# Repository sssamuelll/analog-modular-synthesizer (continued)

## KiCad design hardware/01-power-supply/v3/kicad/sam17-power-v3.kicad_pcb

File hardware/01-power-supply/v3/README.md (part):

# PSU v3 — la primera que se construye

> **ESTADO, 2026-09-04: la v3 NO se pide.** La que se construye es la **v4**
> ([`../v4/`](../v4/)): seis módulos Mean Well IRM encapsulados en vez del
> toroide, con la misma cascada lineal detrás. La gobierna
> [`2026-09-03-fuente-v4-liston-design.md`](../../../docs/superpowers/specs/2026-09-03-fuente-v4-liston-design.md).
>
> Lo que esta carpeta conserva y sigue valiendo: **la cascada** (`U1`/`U2` y la
> isla LT3045/LT3094) con sus puertas, el bus board, la telemetría y el
> bring-up de la cascada. La v4 la hereda entera menos `TR1`, `BR1`, `C_bulk`
> y la franja de red, que se van a la placa R nueva.
>
> **La regla de esta carpeta —«lo que no quede decidido sale con huella y
> `DNP`, nunca con una v4»— NO se reexpide, y el papel de la v4 dice por qué**
> (§0): sus huecos «no son huellas —son chapa, fusible, una placa entera— y
> una regla que no puede aplicarse a sí misma no gobierna». Lo que se impone
> en su lugar es más duro y verificable: **nada de la v4 se manda a fabricar
> con un ítem de §12 abierto**, y eso lo hacen cumplir las puertas de §9, no
> una frase.
>
> Dónde está eso hoy, con número: `hardware/tools/gates.py` (45 en verde, 0 en
> rojo) y `../v4/check_bringup.py` (75 puntos, ninguno medido, porque la placa
> R no existe).
>
> `valle_budget.py` se borró el 2026-09-04: medía el valle de VRAW y la v4 no
> tiene rectificador. Lo sustituye
> [`../v4/margen_budget.py`](../v4/margen_budget.py), que hoy declara un HUECO
> —al riel ultra le faltan 97 mV de margen de entrada en su peor caso— y es
> una decisión abierta, no un fallo de guion.

**Estado:** Fases A (decisiones), B (esquemático), C (placa) y D (chasis)
cerradas. La placa está **ruteada y con DRC en cero**; falta la validación —
que empieza cuando exista la placa física.

> **La v1 y la v2 son diseños de papel.** La v1 se abandonó el 2026-08-17 sin
> fabricar; la v2 llegó a tener gerbers, BOM y CPL generados y tampoco se pidió.
> Ésta es la tercera y la primera que existe como objeto. De ahí su constraint:
> **lo que no quede decidido sale con huella y `DNP`, nunca con una v4.**

## Qué cambia respecto de la v2

La topología de regulación **no se toca**: sigue siendo la cascada de dos etapas
por riel, con las mismas piezas y los mismos setpoints. Lo que cambia es todo lo
que la rodea.

| | v2 | v3 | por qué |
|---|---|---|---|
| **Disipación** | 3 disipadores Fischer individuales | los tabs contra la pared del chasis | Tj de `U2`: 101 → **62 °C** |
| **Colocación de los TO-220** | diagonal opuesta a la isla SMD | en fila sobre un canto, **tabs coplanares** | lo impone la pared, no la estética |
| **Protección** | crowbar en +12 V | **ninguno, en ningún riel** | #118 |
| **Fusible de red** | `F1` en la placa | en el **IEC C14 de la pared** | #130 |
| **Instrumentación** | 6 test points | test points + **isla de telemetría** | spec §4 |

### La protección: no se sustituye, se retira

El crowbar de la v2 protegía contra un fallo del regulador que pusiera VRAW en
el bus. Al rehacer el análisis contra el BOM real (§16.8, reescrita) salieron dos
cosas a la vez:

- **La cascada ya protege sola.** Ningún fallo *simple* pone más de ±13,1 V en el
  bus, que está dentro del máximo absoluto de todos los chips del instrumento. Y
  el pre-regulador no arrastra al post: los LT3045/LT3094 aguantan los 20,54 V de
  VRAW con 1,46 V de margen (ADI Rev. D p.2 / Rev. B p.3).
- **El lazo del crowbar no cerraba con ningún SCR.** El fusible tiene que abrir
  para que el corto sirva de algo, y `F1` subió de 250 mA a 1,6 A en la v2 —
  correctamente, por el inrush del toroide. A los 2,79 A que refleja el fallo,
  IEC 60127 **no obliga** a un fusible T a abrir. El SCR muere en 140 µs; el
  fusible tarda entre 1,3 y 3,9 s.

> El fallo del guardaespaldas es peor que el peligro del que cuida.

Lo que **no** se va con el crowbar: **un TR1 sin fusible térmico embebido no se
compra.** Los 642 W de cualquier corto del secundario son la cuenta que ni `F1`
ni un crowbar cubren, y esto pasa dentro de un recinto cerrado.

## Las puertas

Quince, todas ejecutables, todas recogidas por `hardware/tools/gates.py` sin
tener que apuntarlas en ninguna lista — se añade una escribiendo el fichero,
nunca ampliando un índice que alguien puede olvidar:

| Puerta | Qué pregunta |
|---|---|
| [`check_absmax.py`](check_absmax.py) | ¿sobreviven los módulos a un fallo de regulador? Y antes de eso: ¿la cascada **existe**? |
| [`check_telemetria.py`](check_telemetria.py) | ¿el instrumento sobrevive a medir? Divisores, shunts, direcciones I²C y alimentaciones contra el límite garantizado de cada datasheet |
| [`kicad/check_bom.py`](kicad/check_bom.py) | ¿el BOM y la hoja tienen los mismos designadores? |
| [`kicad/check_netlist.py`](kicad/check_netlist.py) | ¿la isla está **cableada** como dice el contrato? Shunts en serie, divisores en el sentido correcto, masas sin un nodo común |
| [`kicad/check_pcb.py`](kicad/check_pcb.py) | ¿la placa **commiteada** está colocada como dice el script, y su cobre guardado cumple cruces, **masa en árbol sin ni un bucle —vías incluidas—**, cero conexiones abiertas, cero muñones colgando, pista–pad y separación de vías? También vigila la barrera de red, la isla de referencia, la diagonal del lazo y los tres tabs contra la pared |
| [`kicad/check_pcb_mutations.py`](kicad/check_pcb_mutations.py) | ¿las siete mutaciones históricas —pieza movida, cruce, bucle de masa en una capa, bucle que cruza de capa por una vía, muñón colgando, pista sobre pad y vía duplicada— siguen poniendo roja la puerta completa, **cada una por separado y con el número de líneas que su fila declara**? Más los umbrales del filtro de cajas, los rechazos de cobre que no sabe leer, y que una vía de masa quitada deja una conexión abierta |
| [`check_paquete.py`](check_paquete.py) | ¿el paquete de fabricación commiteado es **el de esta placa**? Cruza los trazos de los dos gerbers de cobre contra las pistas, y los taladros del Excellon contra las vías más los pads pasantes. Uno a uno, no por conteo |
| [`check_paquete_mutations.py`](check_paquete_mutations.py) | ¿tocar la placa y **no** regenerar el paquete pone roja esa puerta? Pista nueva, vía nueva, vía podada y pista movida a mano |
| [`check_generador.py`](check_generador.py) | ¿el ruteador escrito a mano sigue corriendo, y produce el cobre que la placa lleva? Corre las cuatro rutas de forma fija en 0,8 s —el laberinto son 180 s y se queda fuera, declarado— y cruza cada tramo y cada vía contra el `.kicad_pcb` |
| [`check_generador_mutations.py`](check_generador_mutations.py) | ¿una aserción rota del generador sale como FALLO con su texto, y un desfase entre guion y placa se ve por los dos lados? |
| [`check_fab.py`](check_fab.py) | ¿lo que se **manda a fábrica** dice lo mismo que la placa? A JLC no se le sube el `.kicad_pcb`: se le suben seis gerbers y un drill que ninguna otra puerta mira |
| [`check_huellas.py`](check_huellas.py) | ¿las huellas dibujadas a mano son las de la **pieza real**? Es geometría, no conectividad: no la ve el ERC, ni el DRC, ni la netlist |
| [`check_red_chasis.py`](check_red_chasis.py) | ¿la red entra por una pieza que **existe**, con un solo fusible, y el chasis tiene su recorte? |
| [`check_bringup.py`](check_bringup.py) | ¿la placa física mide lo que el diseño predijo? 55 puntos con su criterio y su cita |
| ~~`valle_budget.py`~~ | **BORRADO el 2026-09-04.** Medía el valle de VRAW, y la fuente v4 no tiene rectificador ni condensador de bulto: sin ellos no hay valle que medir. Su sustituto es [`../v4/margen_budget.py`](../v4/margen_budget.py), que hace la misma pregunta —¿le llega a `U1`/`U2` bastante tensión para regular?— sobre una cadena de continua |

`check_bom.py` y `check_netlist.py` se reparten huecos a propósito: el primero
pasaría en verde con SDA y SCL cambiados —no falta ni sobra un componente, sobra un cable
en el sitio equivocado— y por eso existe la de netlist.

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
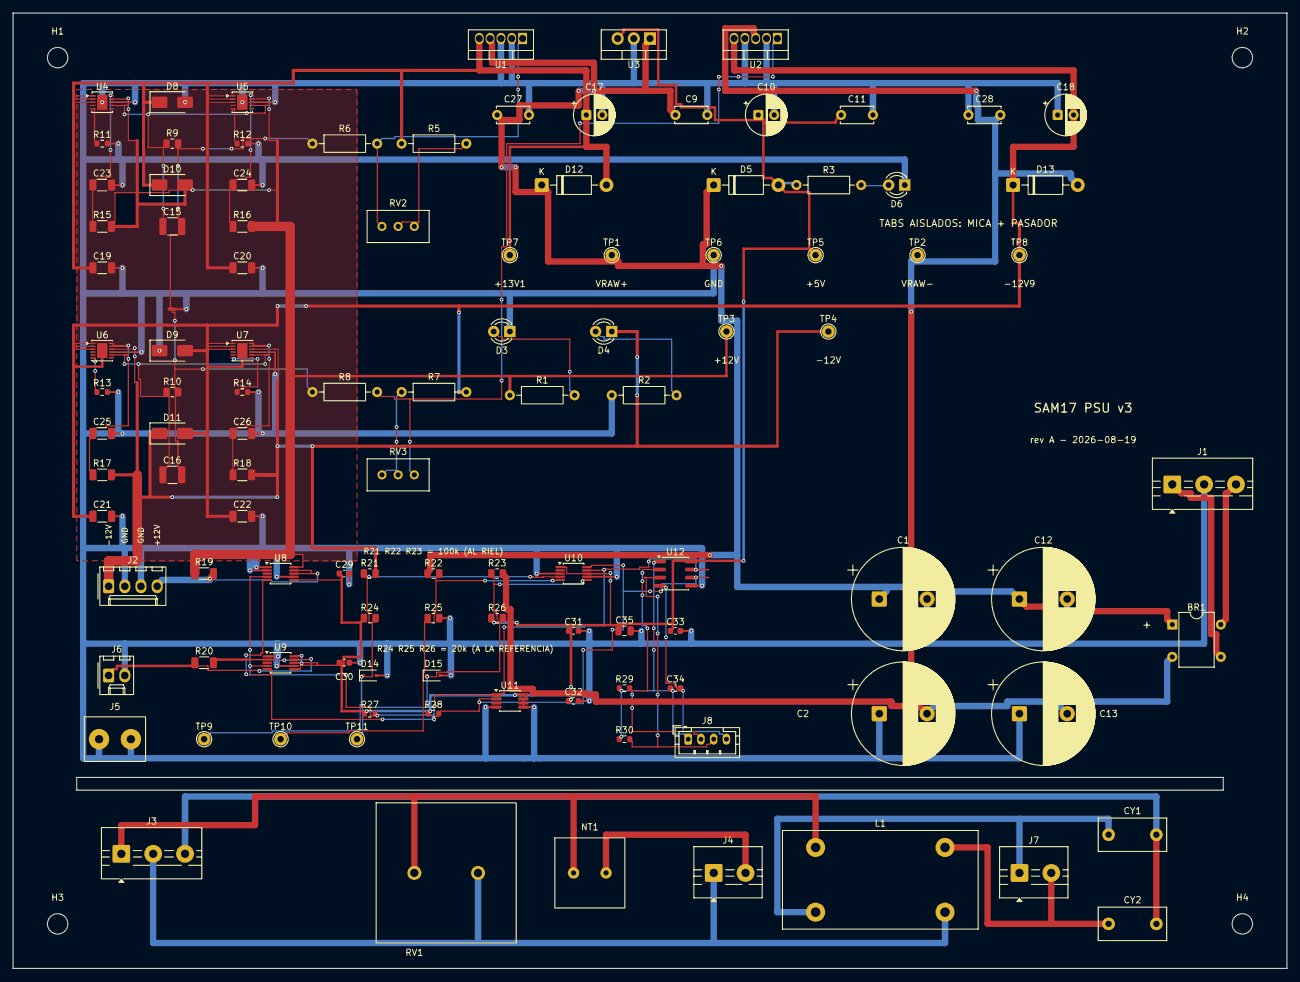
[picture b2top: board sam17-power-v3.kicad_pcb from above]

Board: 2 copper layers, 200.0 x 150.0 mm, 113 parts (0 on the bottom side), 45 nets.

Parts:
BR1: DB207; Diode_Bridge_DIP-4_W7.62mm_P5.08mm
C1, C2, C12, C13: 4700uF/25V electrolitico; CP_Radial_D16.0mm_P7.50mm
C9: 0.33uF ceramico; C_Disc_D5.0mm_W2.5mm_P5.00mm
C10: 100uF/25V electrolitico; CP_Radial_D6.3mm_P2.50mm
C11: 0.1uF ceramico; C_Disc_D5.0mm_W2.5mm_P5.00mm
C15, C16: 22 uF X7R baja fuga 25 V 1210; C_1210_3225Metric
C17, C18: 22 uF; CP_Radial_D6.3mm_P2.50mm
C19, C20, C21, C22, C23, C24, C25, C26: 10 uF X7R 50 V; C_1206_3216Metric
C27, C28: 0.47 uF ceramico; C_Disc_D5.0mm_W2.5mm_P5.00mm
C29, C30, C31, C32, C33, C34: 0.1uF X7R 50V; C_0603_1608Metric
C35: 10uF X7R 25V; C_0805_2012Metric
CY1, CY2: 1 nF clase Y2; C_Disc_D10.5mm_W5.0mm_P7.50mm
D3: LED rojo 3mm; LED_D3.0mm
D4: LED amarillo 3mm; LED_D3.0mm
D5, D12, D13: 1N4001; D_DO-41_SOD81_P10.16mm_Horizontal
D6: LED verde 3mm; LED_D3.0mm
D8, D9: SMAJ15A; D_SMA
D10, D11: SS14; D_SMA
D14, D15: BAT54; D_SOD-323
H1, H2, H3, H4: MountingHole_3.2mm_M3
J1, J3: Barrier block 3 pos; TerminalBlock_MaiXu_MX126-5.0-03P_1x03_P5.00mm
J2: Molex KK-254 4 pos; Molex_KK-254_AE-6410-04A_1x04_P2.54mm_Vertical
J4, J7: Barrier block 2 pos; TerminalBlock_MaiXu_MX126-5.0-02P_1x02_P5.00mm
J5: Vogt 3866A.68 faston 6.3x0.8 PCB; Faston_6.3x0.8mm_PCB_2Leg_P5.0mm
J6: Molex KK-254 2 pos; Molex_KK-254_AE-6410-02A_1x02_P2.54mm_Vertical
J8: JST-PH 4 pos; JST_PH_B4B-PH-K_1x04_P2.00mm_Vertical
JP1: Net tie GNDREF<->GND; NetTie-2_SMD_Pad0.5mm
L1: Choke de modo comun 10 mH / >=0.5 A / 250 VAC; L_CommonMode_Toroid_Vertical_L30.5mm_W15.2mm_Px10.16mm_Py20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
NT1: Ametherm SL10 5R002; NTC_Disc_D10.0mm_W4.0mm_P5.1mm
R1, R2: 2.2k 1/4W; R_Axial_DIN0207_L6.3mm_D2.5mm_P10.16mm_Horizontal
R3: 680R 1/4W; R_Axial_DIN0207_L6.3mm_D2.5mm_P10.16mm_Horizontal
R5: 8.66k 1% 1/4W; R_Axial_DIN0207_L6.3mm_D2.5mm_P10.16mm_Horizontal
R6, R8: 1k 1% 1/4W; R_Axial_DIN0207_L6.3mm_D2.5mm_P10.16mm_Horizontal
R7: 9.09k 1% 1/4W; R_Axial_DIN0207_L6.3mm_D2.5mm_P10.16mm_Horizontal
R9, R10: 120k 1% 100ppm 0805; R_0805_2012Metric
R11, R12: 374 ohm 1%; R_0603_1608Metric
R13, R14: 9.31k 1%; R_0603_1608Metric
R15, R16, R17, R18, R19: 20 mOhm 1%; R_1206_3216Metric
R20: 100 mOhm 1%; R_1206_3216Metric
R21, R22, R23: 100k 0.1% 25 ppm/°C; R_0805_2012Metric
R24, R25, R26: 20k 0.1% 25 ppm/°C; R_0805_2012Metric
R27, R28: 2.2k 1/4W; R_0603_1608Metric
R29, R30: 2.2k 1/4W — DNP; R_0603_1608Metric
RV1: S20K275 / V275LA20A; RV_Disc_D21mm_W5.5mm_P10.0mm
RV2, RV3: 3296W-1-102; Potentiometer_Bourns_3296W_Vertical
TP1, TP2, TP3, TP4, TP5, TP6, TP7, TP8, TP9, TP10, TP11: Punto de prueba; TestPoint_THTPad_D2.0mm_Drill1.0mm
U1: LM2941CT/NOPB; TO-220-5_Vertical
U2: LM2991T/NOPB; TO-220-5_Vertical
U3: LM7805; TO-220-3_Vertical
U4, U5: LT3045EDD#TRPBF; DFN-10-1EP_3x3mm_P0.5mm_EP1.65x2.38mm
U6, U7: LT3094EDD#PBF; DFN-12-1EP_3x3mm_P0.45mm_EP1.65x2.38mm
U8, U9: INA226AIDGSR — monitor I/V I2C 16 bits; MSOP-10_3x3mm_P0.5mm
U10: ADS1115IDGSR — ADC 16 bits 4 canales I2C; MSOP-10_3x3mm_P0.5mm
U11: TMP1075DGKR — sensor de temperatura I2C; VSSOP-8_3x3mm_P0.65mm
U12: ISO1541D — aislador I2C bidireccional; SOIC-8_3.9x4.9mm_P1.27mm

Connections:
+3V3: C34.1, J8.1, R29.1, R30.1, U12.1
+5V: C10.1, C11.1, C29.1, C30.1, C31.1, C32.1, C33.1, C35.1, D5.2, R3.1, R20.2, R24.1, R26.1, R27.1, R28.1, TP5.1, U3.3, U8.6, U9.2, U9.6, U9.8, U9.10, U10.1, U10.8, U11.8, U12.8
+12V: D10.2, R1.1, R15.2, R16.2, R19.1, TP3.1, U4.9, U5.9, U8.10
-12V: D4.1, D11.1, J2.1, R17.2, R18.2, R21.2, TP4.1, U6.10, U7.10
/+5V_M2: J6.1, R20.1, U9.9
/+12V_BUS: J2.4, R19.2, U8.8, U8.9
/+13V1: C17.1, C19.1, C20.1, D8.1, D10.1, D12.2, R5.1, TP7.1, U1.5, U4.1, U4.2, U4.3, U5.1, U5.2, U5.3
/-12V9: C18.2, C21.1, C22.1, D9.2, D11.2, D13.1, R7.2, TP8.1, U2.5, U6.1, U6.2, U6.3, U6.13, U7.1, U7.2, U7.3, U7.13
/GNDREF: C15.2, C16.2, JP1.1, R6.1, R8.1, R9.2, R10.2
/L: J3.1, L1.1, NT1.1, RV1.1
/L_SMPS: CY1.1, J7.1, L1.2
/L_TR: J4.2, NT1.2
/N: J3.2, J4.1, L1.3, RV1.2
/N_SMPS: CY2.1, J7.2, L1.4
/SCL_A: R28.2, U8.5, U9.5, U10.10, U11.2, U12.6
/SCL_D: J8.3, R30.2, U12.3
/SDA_A: R27.2, U8.4, U9.4, U10.9, U11.1, U12.7
/SDA_D: J8.2, R29.2, U12.2
/SEC_A: BR1.3, J1.1
/SEC_B: BR1.4, J1.3
/TAP_-12V: D14.1, R21.1, R24.2, TP9.1, U10.4
/TAP_VRAW+: R22.2, R25.1, TP10.1, U10.5
/TAP_VRAW-: D15.1, R23.1, R26.2, TP11.1, U10.6
/VRAW+: BR1.1, C1.1, C9.1, C12.1, C27.1, D5.1, D12.1, R22.1, TP1.1, U1.4, U3.1
/VRAW-: BR1.2, C2.2, C13.2, C28.2, D13.2, R23.2, TP2.1, U2.3
GND: C1.2, C2.1, C9.2, C10.2, C11.2, C12.2, C13.1, C17.2, C18.1, C19.2, C20.2, C21.2, C22.2, C23.2, C24.2, C25.2, C26.2, C27.2, C28.1, C29.2, C30.2, C31.2, C32.2, C33.2, C35.2, D3.1, D6.1, D8.2, D9.1, D14.2, D15.2, J1.2, J2.2, J2.3, J5.1, J6.2, JP1.2, R2.1, R11.2, R12.2, R13.2, R14.2, R25.2, TP6.1, U1.2, U1.3, U2.2, U2.4, U3.2, U4.8, U4.11, U5.8, U5.11, U6.9, U7.9, U8.1, U8.2, U8.7, U9.1, U9.7, U10.3, U10.7, U11.4, U11.5, U11.6, U11.7, U12.5
GNDD: C34.2, J8.4, U12.4
unnamed: C25.1, R17.1, U6.11, U6.12
unnamed: C26.1, R18.1, U7.11, U7.12
unnamed: D3.2, R1.2
unnamed: D4.2, R2.2
unnamed: D6.2, R3.2
unnamed: R5.2, RV2.1, RV2.2
unnamed: R7.1, RV3.2, RV3.3
unnamed: R6.2, RV2.3, U1.1
unnamed: R8.2, RV3.1, U2.1
unnamed: R11.1, U4.5
unnamed: C23.1, R15.1, U4.10
unnamed: C15.1, R9.1, U4.7, U5.7
unnamed: R12.1, U5.5
unnamed: C24.1, R16.1, U5.10
unnamed: R13.1, U6.6
unnamed: C16.1, R10.1, U6.8, U7.8
unnamed: R14.1, U7.6
PE: CY1.2, CY2.2, J3.3

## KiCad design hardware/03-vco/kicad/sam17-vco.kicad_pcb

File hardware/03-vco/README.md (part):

# Hardware — Módulo 3: la Voz

> [!IMPORTANT]
> ## Esta carpeta documenta la v1 (VCO ×4), y está SUPERADA — 2026-08-22/23
>
> El módulo 3 **deja de ser «el VCO» y pasa a ser la Voz**: dieciséis canales
> completos, cada uno oscilador → filtro → VCA soldado de punta a punta en la
> misma placa, más la bahía asignable. Los módulos 4, 5, 6 y 7 se disuelven
> dentro de él.
>
> | Lo que esta carpeta asume | Lo que se decidió después |
> |---|---|
> | 4 osciladores en una placa de 114 × 124 mm | **16 osciladores en un módulo**, en dos columnas de placas |
> | Sólo VCO: el filtro y el VCA viven fuera | El **canal** es oscilador → filtro → VCA en el mismo cobre |
> | Un micro fuera del módulo compone las palabras del DAC | **Un N657 en el módulo**; del J2 cuelga un micro, no los chips |
> | Panel de 32 jacks, entrada de CV por voz | Muere: en su sitio va la **bahía asignable** de 8 entradas + 8 salidas por dos AD75019 |
> | Sin FM entre osciladores | **Matriz de modulación FM de 16 líneas**: cualquiera modula a cualquiera |
>
> **La v1 nunca se fabricó** — su `notes/medidas.csv` tiene 65 filas y cero
> medidas. Lo que se conserva de ella no es una placa: es un layout validado
> (reparto 2×2, plano de masa medido, escapes del QFN, DRC en 0) y cuatro
> presupuestos ejecutables, y los dos se reutilizan. Por eso este rediseño es
> papel contra papel y sale barato.
>
> **Lo de abajo sigue siendo la mejor documentación del canal individual** —
> convertidor exponencial, referencia, escapes, `TUNE_OUT`— y el bring-up de
> `notes/bring-up.md` sigue siendo válido para lo que describe. Lo que ya no
> vale es el número de canales, el reparto de placas y el panel.
>
> Mandan, en este orden: el
> [spec del módulo de Voz total](../../docs/superpowers/specs/2026-08-23-modulo-voz-total-design.md),
> el [spec de los dieciséis](../../docs/superpowers/specs/2026-08-22-modulo-3-vco-dieciseis-design.md)
> (acta de su junta) y el
> [spec de orquestación](../../docs/superpowers/specs/2026-08-22-vco-orquestacion-design.md).

> Documentación funcional: [`docs/modules/03-vco.md`](../../docs/modules/03-vco.md).
> Diseño y decisiones de la v1: [spec del módulo](../../docs/superpowers/specs/2026-08-16-modulo-3-vco-design.md).
> **Bring-up de la placa física: [`notes/bring-up.md`](notes/bring-up.md).**

## Resumen

**Cuatro voces idénticas en una sola placa**, con un solo juego de mandos —
que no viven aquí: son sensores del panel, y lo que llega a esta placa son
números por el enlace serie. Sustituye a los tres osciladores independientes de
la tesis (Gráficos 25-26).

El núcleo es el **SSI2130** (Sound Semiconductor, 2020), no el CEM3340 de la
tesis. Lo que ese cambio se lleva por delante: la resistencia de compensación
térmica (la lleva el chip), el amplificador de ×2.8 del CV de tono (la entrada
del expo es un nodo de corriente), el mezclador externo y el problema de
amplitudes desiguales (el chip trae un mezclador VCA de 5 canales), y el
generador de seno (lo trae el shaper del propio chip).

Y una cosa que la tesis no tiene: **una salida `TUNE_OUT` digital por voz** —
la onda recortada a nivel lógico con un 74HC14 **en esta placa**. El camino de
afinación es instrumentación, no sonido: va antes del filtro, es permanente, no
se patchea nunca, y al ser cuatro líneas lógicas independientes **las cuatro
voces se miden a la vez**.

## Qué decide este módulo

| | |
|---|---|
| Núcleo | **SSI2130 ×4**, QFN-32. Proveedor único: comprar 6 (4 + 2 repuestos) |
| Afinación | **Trimless**: cero trimmers. La escala la fijan una ADR4525B (2 ppm/°C) y resistencias del 1 % |
| Span nominal | **7.576 octavas** (2.5 V / 16.5 k / 20 µA por octava) sobre las 7 que pide el instrumento: **7.6 % de margen** |
| Resolución | 1 LSB = **0.139 cents**, contra un suelo de medida de 0.5 |
| Suelo de afinación | **0.58 cents** ([`dac_local_budget.py`](dac_local_budget.py)), 3× mejor que con el DAC en el cerebro |
| Mezcla | **dentro del chip**: sierra/tri/pulso/seno con 4 CV compartidos, control lineal 0-50 µA |
| Referencia | **UNA** para toda la placa (ADR4525BRZ). Las tres internas de los DAC **se apagan por firmware** (registro `0111`) |
| Digital | 3× AD5686R en **cadena soldada** (DCEN): 9 canales usados + 3 de reserva |
| Telemetría | TMP1075 a **2.12 mm del cuerpo de U2**, EEPROM 24AA02E48 con ID único, 15 test points |
| Consumo | **~35 mA en +12 V, ~15 mA en −12 V** — contra los ~120 mA de la versión CEM3340+LM13700 |
| Patch bay | 8 jacks: CV-IN ×4 (normalizados a 0 V) y salida de voz ×4 (normalizadas al VCF en el módulo 5) |

**La apuesta que hay que cobrar en la placa**: el margen del 7.6 % de span
existe para no llevar trimmers. Nadie garantiza la dispersión chip a chip del
convertidor exponencial del SSI2130, así que **hasta que no se mida no está
demostrado**. El bodge previsto si una voz cae fuera es cambiar **su**
`R_PITCH` — una resistencia, no un re-spin. Procedimiento y valores en el
**Paso 5** de [`notes/bring-up.md`](notes/bring-up.md).

## Componentes principales

| Función | Componente | Ref |
|---------|------------|-----|
| Núcleo VCO + mezclador + seno | **SSI2130**, QFN-32 | U1-U4 |
| DAC 16 bits ×4, en cadena | **AD5686RBRUZ** ×3 | U5-U7 |
| La referencia de la placa | **ADR4525BRZ**, 2.5 V, 2 ppm/°C | U8 |
| Transimpedancia MIX OUT → jack | **TL074H** (el H por deriva) | U9 |
| `TUNE_OUT` ×4 a 3.3 V | **74HC14** Schmitt | U10 |
| Alimentación local +5 V / +3.3 V | L78L05 → LD1117S33 | U11, U12 |
| Telemetría | TMP1075 (I²C 0x48), 24AA02E48 (0x50) | U13, U14 |

BOM completo, con los porqués: [`bom.csv`](bom.csv).

## El mazo digital J2 — contrato del enlace

IDC 2×6, niveles 3.3 V. **Mismo conector y mismas posiciones en los módulos 5,
6 y 7**; cada uno usa las señales que le tocan y recibe su propio CS.

| 1 | 2 | 3 | 4 | 5 | 6 |
|---|---|---|---|---|---|
| `SCLK` | `GNDD` | `MOSI` | `MISO` | `CS3` | `GNDD` |

| 7 | 8 | 9 | 10 | 11 | 12 |
|---|---|---|---|---|---|
| `SDA` | `SCL` | `TUNE_OUT_1` | `TUNE_OUT_2` | `TUNE_OUT_3` | `TUNE_OUT_4`|

SPI modo 1, ≤10 MHz. **CS3 abajo durante los 72 relojes de la trama entera** (3
chips × 24 bits); el flanco de subida carga los tres. **El primer word que sale
por MOSI acaba en U7 y el último se queda en U5**: orden de transmisión
`[U7][U6][U5]`.

Canales del DAC: **U5** A-D = tono de las voces 1-4. **U6** A = PWM (compartido),
B/C/D = mezcla sierra/tri/pulso. **U7** A = mezcla de seno, B/C/D de reserva.

## La placa

114 × 124 mm, **4 capas**. `In1` es un plano GNDA sólido, en una sola isla al
100 % — por ahí no pasa ni una pista, solo vías. La masa digital es una **isla**
en la esquina de J2, con 3.00 mm de hueco.

Colocación en **cuadro 2×2**, no en fila: los 3 DAC y la referencia caben en el
hueco central y las 4 voces quedan a la misma distancia del DAC (peor par
**43.2 mm**, dentro de la cota de `dac_local_budget.py`). En fila el peor par se
iba a 85 mm.

El **EP de cada SSI2130 queda aislado a propósito** — sin red, sin vía, sin unión
al plano. Lo prohíbe el datasheet (pág. 6): unirlo a masa convierte el land en
una antena de acoplo entre las cuatro voces.

Los porqués completos viven en los docstrings de
[`kicad/build_schematic.py`](kicad/build_schematic.py) y
[`kicad/build_pcb.py`](kicad/build_pcb.py). El ruteo lo hace Freerouting, no un
ruteador casero.

## Estructura del directorio

```
03-vco/
├── README.md
├── bom.csv                     30 líneas, cada una con su porqué
├── dac_local_budget.py         Qué gana el DAC viviendo en esta placa
├── kicad/
│   ├── build_schematic.py      Genera sam17-vco.kicad_sch (s-expr + kicad-cli)
│   ├── build_pcb.py            Genera sam17-vco.kicad_pcb (pcbnew + Freerouting)
│   ├── check_netlist.py        Conectividad contra el diseño declarado
│   ├── check_bom.py            Cruce esquemático <-> bom.csv
│   ├── sam17.kicad_sym         Símbolos propios: SSI2130 y AD5686RBRUZ
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
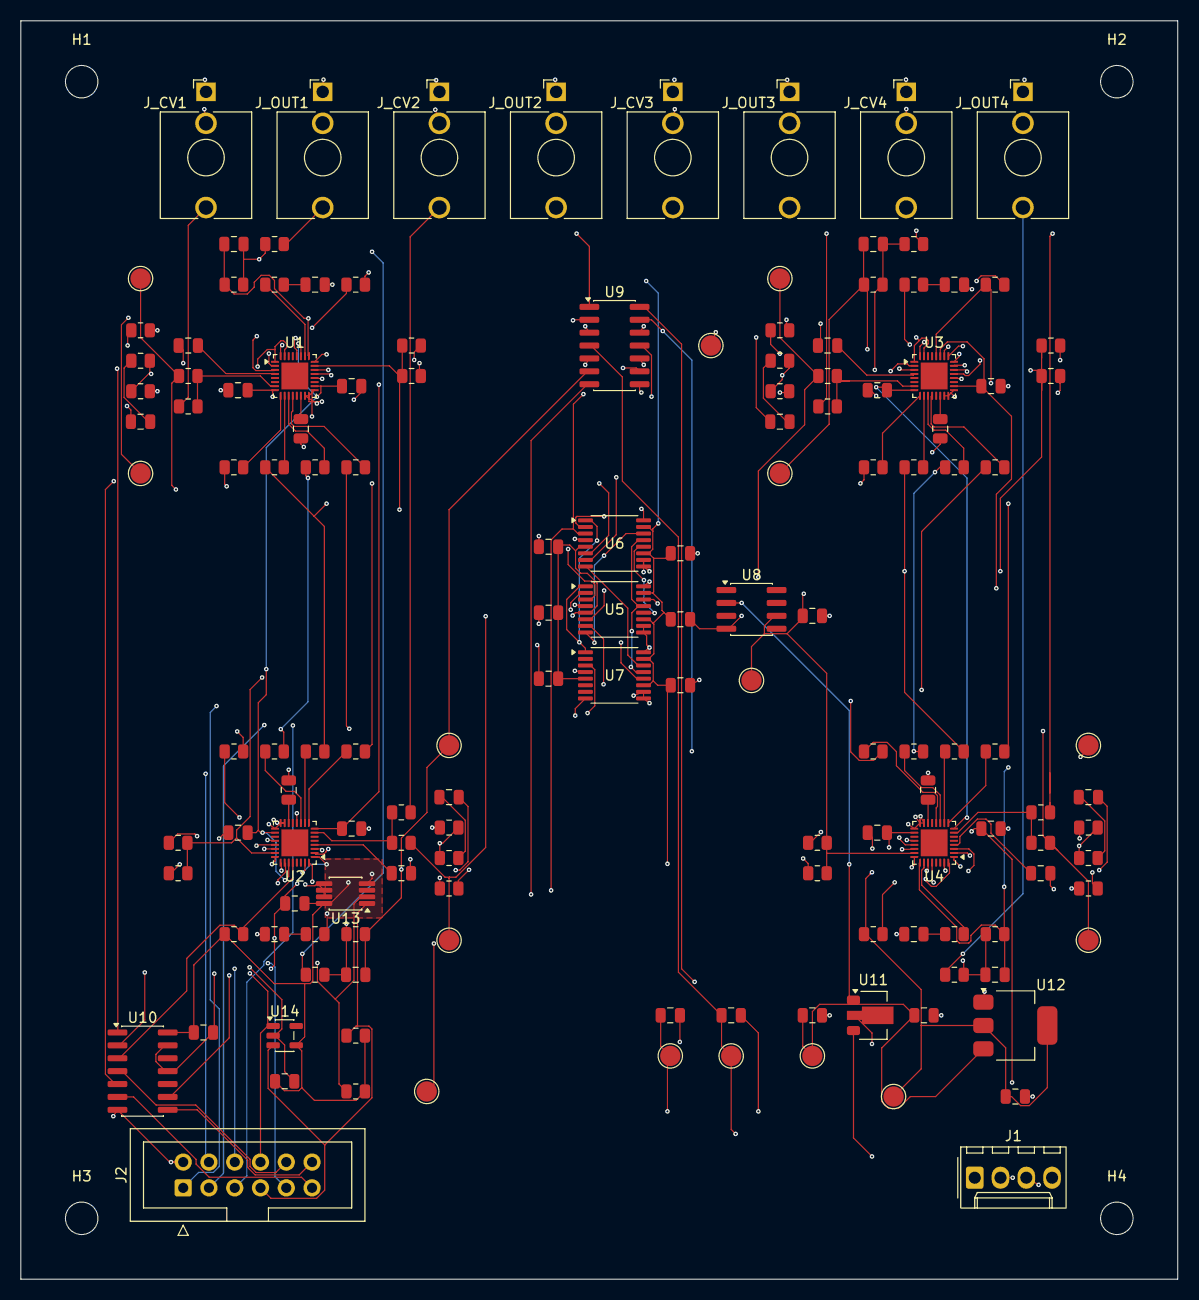
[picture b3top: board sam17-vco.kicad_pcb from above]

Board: 4 copper layers, 114.0 x 124.0 mm, 148 parts (0 on the bottom side), 112 nets.

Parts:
C8, C9, C10, C11, C12, C13, C14, C15, C16, C17, C18, C19, C20, C21, C22, C23, C24, C25, C26, C27, C28, C29, C30: C_0805_2012Metric
C_AC1A, C_AC1B, C_AC2A, C_AC2B, C_AC3A, C_AC3B, C_AC4A, C_AC4B: C_0805_2012Metric
C_BW1, C_BW2, C_BW3, C_BW4: C_0805_2012Metric
C_IV1, C_IV2, C_IV3, C_IV4: C_0805_2012Metric
C_TCAP1, C_TCAP2, C_TCAP3, C_TCAP4: C_0805_2012Metric
H1, H2, H3, H4: MountingHole_3.2mm_M3
J1: Molex_KK-254_AE-6410-04A_1x04_P2.54mm_Vertical
J2: IDC-Header_2x06_P2.54mm_Vertical
J_CV1, J_CV2, J_CV3, J_CV4: Jack_3.5mm_QingPu_WQP-PJ398SM_Vertical_CircularHo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; Jack_3.5mm_QingPu_WQP-PJ398SM_Vertical_CircularHoles
J_OUT1, J_OUT2, J_OUT3, J_OUT4: Jack_3.5mm_QingPu_WQP-PJ398SM_Vertical_CircularHo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; Jack_3.5mm_QingPu_WQP-PJ398SM_Vertical_CircularHoles
R_BW1, R_BW2, R_BW3, R_BW4: R_0805_2012Metric
R_CVIN1, R_CVIN2, R_CVIN3, R_CVIN4: R_0805_2012Metric
R_I2C1, R_I2C2: R_0805_2012Metric
R_IV1, R_IV2, R_IV3, R_IV4: R_0805_2012Metric
R_LIN1, R_LIN2, R_LIN3, R_LIN4: R_0805_2012Metric
R_MIX1A, R_MIX1B, R_MIX1C, R_MIX1D, R_MIX2A, R_MIX2B, R_MIX2C, R_MIX2D, R_MIX3A, R_MIX3B, R_MIX3C, R_MIX3D, R_MIX4A, R_MIX4B, R_MIX4C, R_MIX4D: R_0805_2012Metric
R_OUT1, R_OUT2, R_OUT3, R_OUT4: R_0805_2012Metric
R_PITCH1, R_PITCH2, R_PITCH3, R_PITCH4: R_0805_2012Metric
R_SCALE1, R_SCALE2, R_SCALE3, R_SCALE4: R_0805_2012Metric
R_SIN402_1, R_SIN402_2, R_SIN402_3, R_SIN402_4, R_SIN475A_1, R_SIN475A_2, R_SIN475A_3, R_SIN475A_4, R_SIN475B_1, R_SIN475B_2, R_SIN475B_3, R_SIN475B_4: R_0805_2012Metric
R_SQ1, R_SQ2, R_SQ3, R_SQ4: R_0805_2012Metric
TP1, TP2, TP3, TP4, TP5, TP6, TP7, TP8, TP9, TP10, TP11, TP12, TP13, TP14, TP15: TestPoint_Pad_D2.0mm
U1, U2, U3, U4: QFN-32-1EP_4x4mm_P0.4mm_EP2.65x2.65mm
U5, U6, U7: TSSOP-16_4.4x5mm_P0.65mm
U8: SOIC-8_3.9x4.9mm_P1.27mm
U9, U10: SOIC-14_3.9x8.7mm_P1.27mm
U11: SOT-89-3
U12: SOT-223-3_TabPin2
U13: VSSOP-8_3x3mm_P0.65mm
U14: SOT-23-5

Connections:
+3V3_LOC: C9.1, C13.1, C15.1, C17.1, C18.1, C19.1, C20.1, R_I2C1.2, R_I2C2.2, R_SQ1.2, R_SQ2.2, R_SQ3.2, R_SQ4.2, TP4.1, U5.11, U5.15, U6.11, U6.15, U7.11, U7.15, U10.14, U12.2, U13.8, U14.4
+5V_LOC: C8.1, C10.1, C12.1, C14.1, C16.1, C21.1, C22.1, C23.1, C24.1, TP3.1, U1.18, U1.27, U2.18, U2.27, U3.18, U3.27, U4.18, U4.27, U5.5, U6.5, U7.5, U8.2, U11.1, U12.3
+12V: C25.1, J1.1, TP1.1, U9.4, U11.3
-12V: C26.1, C27.1, C28.1, C29.1, C30.1, J1.4, TP2.1, U1.8, U2.8, U3.8, U4.8, U9.11
CVIN_1: J_CV1.T, R_CVIN1.1
CVIN_2: J_CV2.T, R_CVIN2.1
CVIN_3: J_CV3.T, R_CVIN3.1
CVIN_4: J_CV4.T, R_CVIN4.1
CV_PITCH_1: R_PITCH1.1, TP6.1, U5.3
CV_PITCH_2: R_PITCH2.1, TP7.1, U5.2
CV_PITCH_3: R_PITCH3.1, TP8.1, U5.6
CV_PITCH_4: R_PITCH4.1, TP9.1, U5.7
DAC_LINK_12: U5.8, U6.14
DAC_LINK_23: U6.8, U7.14
GNDA: C8.2, C9.2, C10.2, C11.2, C12.2, C13.2, C14.2, C15.2, C16.2, C17.2, C21.2, C22.2, C23.2, C24.2, C25.2, C26.2, C27.2, C28.2, C29.2, C30.2, C_BW1.2, C_BW2.2, C_BW3.2, C_BW4.2, C_TCAP1.2, C_TCAP2.2, C_TCAP3.2, C_TCAP4.2, J1.2, J1.3, J_CV1.S, J_CV1.TN, J_CV2.S, J_CV2.TN, J_CV3.S, J_CV3.TN, J_CV4.S, J_CV4.TN, J_OUT1.S, J_OUT2.S, J_OUT3.S, J_OUT4.S, R_SIN475A_1.2, R_SIN475A_2.2, R_SIN475A_3.2, R_SIN475A_4.2, R_SIN475B_1.2, R_SIN475B_2.2, R_SIN475B_3.2, R_SIN475B_4.2, TP14.1, U1.15, U1.16, U1.17, U1.20, U2.15, U2.16, U2.17, U2.20, U3.15, U3.16, U3.17, U3.20, U4.15, U4.16, U4.17, U4.20, U5.4, U5.9, U5.10, U5.16, U6.4, U6.9, U6.10, U6.16, U7.4, U7.9, U7.10, U7.16, U8.4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
GNDD: C18.2, C19.2, C20.2, J2.2, J2.6, TP15.1, U10.7, U10.11, U10.13, U13.4, U13.5, U13.6, U13.7, U14.2
I2C_SCL: J2.8, R_I2C2.1, U13.2, U14.1
I2C_SDA: J2.7, R_I2C1.1, U13.1, U14.3
IVO_1: C_IV1.2, R_IV1.2, R_OUT1.1, U9.1
IVO_2: C_IV2.2, R_IV2.2, R_OUT2.1, U9.7
IVO_3: C_IV3.2, R_IV3.2, R_OUT3.1, U9.8
IVO_4: C_IV4.2, R_IV4.2, R_OUT4.1, U9.14
MIXO_1: C_IV1.1, R_IV1.1, TP10.1, U1.25, U9.2
MIXO_2: C_IV2.1, R_IV2.1, TP11.1, U2.25, U9.6
MIXO_3: C_IV3.1, R_IV3.1, TP12.1, U3.25, U9.9
MIXO_4: C_IV4.1, R_IV4.1, TP13.1, U4.25, U9.13
MIX_PULSE: R_MIX1C.1, R_MIX2C.1, R_MIX3C.1, R_MIX4C.1, U6.7
MIX_SAW: R_MIX1B.1, R_MIX2B.1, R_MIX3B.1, R_MIX4B.1, U6.2
MIX_SINE: R_MIX1D.1, R_MIX2D.1, R_MIX3D.1, R_MIX4D.1, U7.3
MIX_TRI: R_MIX1A.1, R_MIX2A.1, R_MIX3A.1, R_MIX4A.1, U6.6
N2M_1: C_AC1A.2, R_SIN402_1.1
N2M_2: C_AC2A.2, R_SIN402_2.1
N2M_3: C_AC3A.2, R_SIN402_3.1
N2M_4: C_AC4A.2, R_SIN402_4.1
N2_1: R_SIN402_1.2, R_SIN475A_1.1, U1.2
N2_2: R_SIN402_2.2, R_SIN475A_2.1, U2.2
N2_3: R_SIN402_3.2, R_SIN475A_3.1, U3.2
N2_4: R_SIN402_4.2, R_SIN475A_4.1, U4.2
N3_1: R_SIN475B_1.1, U1.3
N3_2: R_SIN475B_2.1, U2.3
N3_3: R_SIN475B_3.1, U3.3
N3_4: R_SIN475B_4.1, U4.3
N4_1: C_AC1B.2, U1.4
N4_2: C_AC2B.2, U2.4
N4_3: C_AC3B.2, U3.4
N4_4: C_AC4B.2, U4.4
N7_1: R_CVIN1.2, R_PITCH1.2, U1.7
N7_2: R_CVIN2.2, R_PITCH2.2, U2.7
N7_3: R_CVIN3.2, R_PITCH3.2, U3.7
N7_4: R_CVIN4.2, R_PITCH4.2, U4.7
N9_1: R_MIX1A.2, U1.9
N9_2: R_MIX2A.2, U2.9
N9_3: R_MIX3A.2, U3.9
N9_4: R_MIX4A.2, U4.9
N10_1: R_MIX1B.2, U1.10
N10_2: R_MIX2B.2, U2.10
N10_3: R_MIX3B.2, U3.10
N10_4: R_MIX4B.2, U4.10
N11_1: R_MIX1C.2, U1.11
N11_2: R_MIX2C.2, U2.11
N11_3: R_MIX3C.2, U3.11
N11_4: R_MIX4C.2, U4.11
N12_1: R_MIX1D.2, U1.12
N12_2: R_MIX2D.2, U2.12
N12_3: R_MIX3D.2, U3.12
N12_4: R_MIX4D.2, U4.12
N14_1: C_TCAP1.1, U1.14
N14_2: C_TCAP2.1, U2.14
N14_3: C_TCAP3.1, U3.14
N14_4: C_TCAP4.1, U4.14
N21_1: R_LIN1.2, U1.21
N21_2: R_LIN2.2, U2.21
N21_3: R_LIN3.2, U3.21
N21_4: R_LIN4.2, U4.21
N22_1: R_SCALE1.2, U1.22
N22_2: R_SCALE2.2, U2.22
N22_3: R_SCALE3.2, U3.22
N22_4: R_SCALE4.2, U4.22
N26M_1: C_BW1.1, R_BW1.2
N26M_2: C_BW2.1, R_BW2.2
N26M_3: C_BW3.1, R_BW3.2
N26M_4: C_BW4.1, R_BW4.2
N26_1: R_BW1.1, U1.26
N26_2: R_BW2.1, U2.26
N26_3: R_BW3.1, U3.26
N26_4: R_BW4.1, U4.26
PWM_CV: U1.32, U2.32, U3.32, U4.32, U6.3
SINEO_1: C_AC1B.1, U1.24
SINEO_2: C_AC2B.1, U2.24
SINEO_3: C_AC3B.1, U3.24
SINEO_4: C_AC4B.1, U4.24
SPI_CS3: J2.5, U5.13, U6.13, U7.13
SPI_MISO: J2.4, U7.8
SPI_MOSI: J2.3, U5.14
SPI_SCLK: J2.1, U5.12, U6.12, U7.12
SQ_1: R_SQ1.1, U1.28, U10.1
SQ_2: R_SQ2.1, U2.28, U10.3
SQ_3: R_SQ3.1, U3.28, U10.5
SQ_4: R_SQ4.1, U4.28, U10.9
TRI_1: C_AC1A.1, U1.1, U1.31
TRI_2: C_AC2A.1, U2.1, U2.31
TRI_3: C_AC3A.1, U3.1, U3.31
TRI_4: C_AC4A.1, U4.1, U4.31
TUNE_OUT_1: J2.9, U10.2
TUNE_OUT_2: J2.10, U10.4
TUNE_OUT_3: J2.11, U10.6
TUNE_OUT_4: J2.12, U10.8
VOICE_OUT_1: J_OUT1.T, R_OUT1.2
VOICE_OUT_2: J_OUT2.T, R_OUT2.2
VOICE_OUT_3: J_OUT3.T, R_OUT3.2
VOICE_OUT_4: J_OUT4.T, R_OUT4.2
VREF_2V5: C11.1, R_LIN1.1, R_LIN2.1, R_LIN3.1, R_LIN4.1, R_SCALE1.1, R_SCALE2.1, R_SCALE3.1, R_SCALE4.1, TP5.1, U1.23, U2.23, U3.23, U4.23, U5.1, U6.1, U7.1, U8.6

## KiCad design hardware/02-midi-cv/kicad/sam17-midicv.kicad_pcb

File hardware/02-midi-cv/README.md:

# Hardware — Módulo 2: MIDI/CV

> [!IMPORTANT]
> ## Este diseño está SUPERADO — 2026-08-17
>
> Lo que hay en esta carpeta es el módulo 2 **v1**: Raspberry Pi 3B+, DAC
> AD5686R a bordo, LCD 16×2 y cuatro pulsadores. Tres decisiones posteriores lo
> invalidaron:
>
> | Lo que esta placa asume | Lo que se decidió después |
> |---|---|
> | El Pi dentro del instrumento | La computadora se queda **fuera** — `architecture-compute.md` §1 |
> | El DAC aquí, un cable por CV | Los DAC **viven en cada módulo** — `architecture-poly.md` §8 |
> | LCD 16×2 + 4 pulsadores + cabecera de 40 pines | Cabeza mínima y pantalla inalámbrica |
>
> **No se rutea, se reemplaza.** El sucesor es el **módulo 2 v2** sobre
> **RP2350B**, especificado en
> [`docs/superpowers/specs/2026-08-17-nucleo-digital-design.md`](../../docs/superpowers/specs/2026-08-17-nucleo-digital-design.md),
> y **su contrato ya está escrito y en verde**: modelo de parámetros,
> descriptor, protocolo, descubrimiento, partes, presets y los dos motores de
> análisis viven en [`software/nucleo/`](../../software/nucleo), verificados con
> `cargo test` sin haber tocado una placa.
> El respin **disuelve el issue #22** en vez de resolverlo: la congestión que
> dejó 17 redes al aire eran justo las seis líneas del LCD, los cuatro botones y
> la cabecera del Pi.
>
> **Qué sobrevive y no hay que re-derivar:** el presupuesto de afinación
> ([`tuning_budget.py`](tuning_budget.py)), el de autoafinado
> ([`autotune_budget.py`](autotune_budget.py) — ya actualizado al PIO del
> RP2350, ver §5.1 de la spec), la lección de las masas partidas, y el gate de
> dos MOSFET para que el reposo al arrancar sea bajo.
>
> **Qué muere con el Pi:** la PCB, y el firmware de
> [`software/midi-cv/`](../../software/midi-cv), que es Python con `RPi.GPIO`,
> `spidev` y `RPLCD`. Eso deja sin objeto la mitad del issue #18.
>
> **Enmienda del 2026-08-30 (D1):** el sucesor del recuadro ya no es un
> RP2350B: el módulo 2 v2 se especifica sobre **STM32N657** (spec del hub
> N657, D1). Lo demás de este recuadro —qué sobrevive y qué muere con el
> Pi— no cambia; el «PIO del RP2350» del autoafinado quedó superado el
> 2026-08-26 (capturas de TIM del N657, enmienda de `autotune_budget.py`).

> Documentación funcional: [`docs/modules/02-midi-cv.md`](../../docs/modules/02-midi-cv.md).
> Firmware: [`software/midi-cv/`](../../software/midi-cv).

## Resumen

El único módulo digital del sintetizador. Combina un Raspberry Pi 3B+ con un
DAC AD5686R (16-bit, cuádruple) para generar 3 salidas CV (1 V/oct) y 1
GATE digital (10 V) a partir de mensajes MIDI USB.

## Componentes principales

| Función | Componente |
|---------|------------|
| Procesamiento + USB MIDI | Raspberry Pi 3B+ |
| Conversión D/A (4 canales 16-bit) | AD5686R |
| Buffer/escalado CV | TL074 (op-amp) |
| Pantalla menú | LCD 16×2 (HD44850 / HD44780 compat.) |
| Navegación | 4 pulsadores táctiles |

## Pinout (ver `docs/modules/02-midi-cv.md`)

GPIO BCM: UP=4, DOWN=17, BACK=16, ENTER=26, GATE=27, DAC RESET=6.
LCD: RS=25, EN=24, D4=23, D5=18, D6=15, D7=14.
SPI: bus 0, device 1, mode `0b01`, max 50 MHz.

## Qué decide este módulo

Es la fuente del CV de tono, así que su error se suma al de la masa del bus.
El presupuesto está en [`tuning_budget.py`](tuning_budget.py) y sale a
**1.68 cents**, de los cuales **1.21 siguen siendo la masa** del bus board.

Lo que no era obvio: los errores **estáticos** suman **103 cents** y no cuenta
ninguno, porque la tabla de afinación (`tuning.json`) los absorbe enteros. Solo
importa lo que deriva *después* de calibrar. De ahí salen las tres decisiones
del módulo — ver [`notes/design-notes.md`](notes/design-notes.md).

| | |
|---|---|
| Rango del CV | **0–7 V** (la tesis usa 3–10; §3 de las notas) |
| Resolución | 1 LSB = **0.128 cents** |
| Amplificador | **TL074H**, no TL074 — la deriva es 9× mejor |
| Masas | **`GNDA` y `GNDD` separadas**, se unen solo en la estrella del módulo 1 |
| `VLOGIC` del DAC | **+3V3**, no +5 V: si no, V_IH = 3.5 V y el Pi da 3.3 |
| GATE | dos MOSFET, para que el reposo al arrancar sea **bajo** |

## Estructura del directorio

```
02-midi-cv/
├── README.md
├── bom.csv
├── tuning_budget.py     Presupuesto de afinación, ejecutable y con aserciones
├── kicad/
│   ├── build_schematic.py   Genera sam17-midicv.kicad_sch (sin MCP: kicad-cli)
│   ├── check_netlist.py     Conectividad contra el diseño declarado
│   ├── check_bom.py         Cruce esquemático <-> bom.csv
│   └── sam17.kicad_sym      Símbolo propio del AD5686R (KiCad no lo trae)
├── schematics/
├── pcb/        (pendiente)
└── notes/design-notes.md
```

## Estado

- [x] Presupuesto de afinación cerrado — **1.68 cents** de 5
- [x] Piezas verificadas contra datasheet primario: pinout TSSOP del AD5686R
      (que **no** es el del LFCSP), recorrido y deriva del TL074H, `VLOGIC`
- [x] Esquemático en KiCad — 42 componentes, **ERC 0 infracciones**
- [x] Netlist verificado: 63 redes, masas separadas, gate no inversor
- [x] `bom.csv` cuadra designador a designador (42/42)
- [~] **PCB congelada con 17 redes sin rutear** — colocación cerrada y
      verificada, las dos masas partidas con **4.00 mm de hueco medido**, plano
      analógico entero en una sola isla, DRC **0 infracciones**. `build_pcb.py`
      sale con error a propósito ([§10](notes/design-notes.md)).
      **Ya no se va a cerrar**: la sustituye el respin en STM32N657
- [x] ~~Firmware: el cambio de rango a 0–7 V~~ — sin objeto, el firmware del Pi
      muere con el Pi (issue #18)
- [x] ~~Diseño térmico del Raspberry Pi~~ — sin objeto, no hay Pi
- [ ] ~~Medir la deriva del CV con la temperatura~~ · ~~Validación SPI con
      osciloscopio~~ — se heredan al bring-up del **v2**, no a esta placa

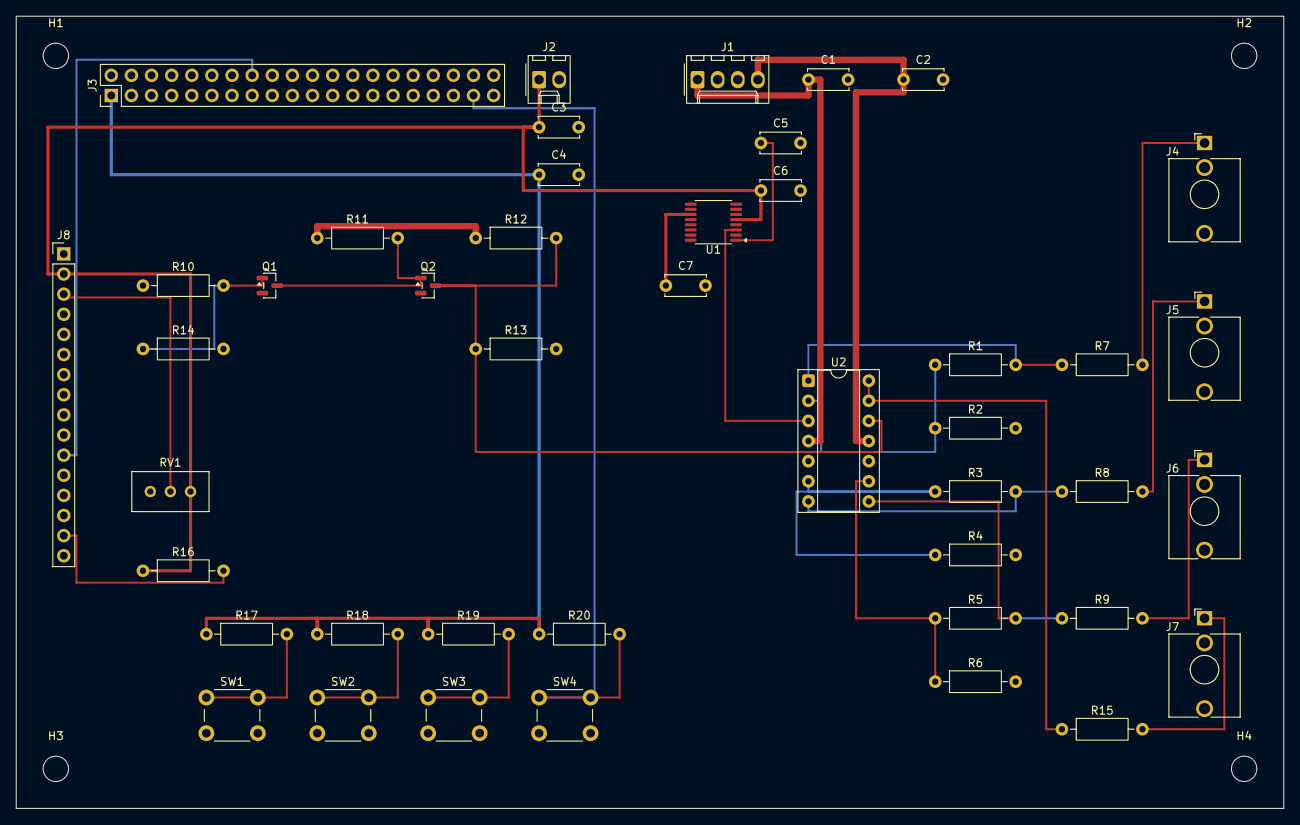
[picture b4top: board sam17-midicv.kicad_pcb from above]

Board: 2 copper layers, 160.0 x 100.0 mm, 48 parts (0 on the bottom side), 41 nets.

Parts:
C1, C2, C3, C4, C5, C6, C7: C_Disc_D5.0mm_W2.5mm_P5.00mm
H1, H2, H3, H4: MountingHole_3.2mm_M3
J1: Molex_KK-254_AE-6410-04A_1x04_P2.54mm_Vertical
J2: Molex_KK-254_AE-6410-02A_1x02_P2.54mm_Vertical
J3: PinHeader_2x20_P2.54mm_Vertical
J4, J5, J6, J7: Jack_3.5mm_QingPu_WQP-PJ398SM_Vertical_CircularHo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; Jack_3.5mm_QingPu_WQP-PJ398SM_Vertical_CircularHoles
J8: PinHeader_1x16_P2.54mm_Vertical
Q1, Q2: SOT-23
R1, R2, R3, R4, R5, R6, R7, R8, R9, R10, R11, R12, R13, R14, R15, R16, R17, R18, R19, R20: R_Axial_DIN0207_L6.3mm_D2.5mm_P10.16mm_Horizontal
RV1: Potentiometer_Bourns_3296W_Vertical
SW1, SW2, SW3, SW4: SW_PUSH_6mm
U1: TSSOP-16_4.4x5mm_P0.65mm
U2: DIP-14_W7.62mm_Socket

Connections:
+3V3: C4.1, C7.1, J3.1, R17.1, R18.1, R19.1, R20.1, U1.11
+5V: C3.1, C6.1, J2.1, J8.2, R16.1, RV1.1, U1.5
+12V: C1.1, J1.1, R11.1, R12.1, U2.4
-12V: C2.1, J1.4, U2.11
BTN_BACK: J3.36, R19.2, SW3.1
BTN_DOWN: J3.11, R18.2, SW2.1
BTN_ENTER: J3.37, R20.2, SW4.1
BTN_UP: J3.7, R17.2, SW1.1
CV1: J4.S, R7.2
CV2: J5.S, R8.2
CV3: J6.S, R9.2
DAC_A: U1.3, U2.3
DAC_B: U1.2, U2.5
DAC_C: U1.6, U2.10
DAC_RESET: J3.31, U1.15
GATE_12: Q2.3, R12.2, R13.1, U2.12
GATE_G: Q1.1, R10.2, R14.1
GATE_INV: Q1.3, Q2.1, R11.2
GATE_IO: J3.13, R10.1
GATE_OUT: J7.S, R15.2
GATE_OUT_B: R15.1, U2.13, U2.14
GNDA: C1.2, C2.2, C5.2, C6.2, C7.2, J1.2, J1.3, J4.T, J5.T, J6.T, J7.T, R2.2, R4.2, R6.2, U1.4, U1.9, U1.10, U1.16
GNDD: C3.2, C4.2, J2.2, J3.6, J3.9, J3.14, J3.20, J3.25, J3.30, J3.34, J3.39, J8.1, J8.5, J8.16, Q1.2, Q2.2, R13.2, R14.2, RV1.3, SW1.2, SW2.2, SW3.2, SW4.2
LCD_BLA: J8.15, R16.2
LCD_D4: J3.16, J8.11
LCD_D5: J3.12, J8.12
LCD_D6: J3.10, J8.13
LCD_D7: J3.8, J8.14
LCD_EN: J3.18, J8.6
LCD_RS: J3.22, J8.4
LCD_VO: J8.3, RV1.2
unnamed: R1.2, R7.1, U2.1
unnamed: R3.2, R8.1, U2.7
unnamed: R5.2, R9.1, U2.8
unnamed: R1.1, R2.1, U2.2
unnamed: R3.1, R4.1, U2.6
unnamed: R5.1, R6.1, U2.9
SCLK: J3.23, U1.12
SDIN: J3.19, U1.14
SPI_CE1: J3.26, U1.13
VREF: C5.1, U1.1
